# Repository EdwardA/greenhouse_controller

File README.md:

# greenhouse_controller
Arduino and Linux based sensor and control network
As part of a belated Devember

This project is to design and implement a distributed sensor and control system to automate an indoors growing environment.

As the network is designed to automate high volume growing enviroments. Each growing bed utalises its own slave unit which manages and records the data from that bed while passing the data back to the main controller for logging. While also reciving data back from the controller to control the actuators on that bed.

The system will be designed to be expandable very quickly and easily, by adding new 'beds' to the network.

---Slave board---

--Sensors--
Light (intensity and colour)
soil moisture
Soil temperature
Air temperature
RTC (Real Time Clock)

--Control--
Growing lights (LED, RGB)
Sprinklers (Three per bed)
Emergancy Stop
Heater

--Conectivity--
USB (mainly for debug and programming)
Ethernet (Comunicating with the controller)

---Controller Board---
Recive sensor data from slave boards, and send changes in paramaters back.
Most likely Python script
ROS?
Recive changes in parameters from user and distribute relevant commands to slave units.

The slave unit is based off the ATMEGA 1284 chip, using a 3rd party arduino bootloader.

The slave is programed thanks to the use of the bootloader found here: http://www.leonardomiliani.com/repository/package_leonardomiliani.com_index.json

Light sensor = TCSP3200, code based off the example given at: https://randomnerdtutorials.com/arduino-color-sensor-tcs230-tcs3200/

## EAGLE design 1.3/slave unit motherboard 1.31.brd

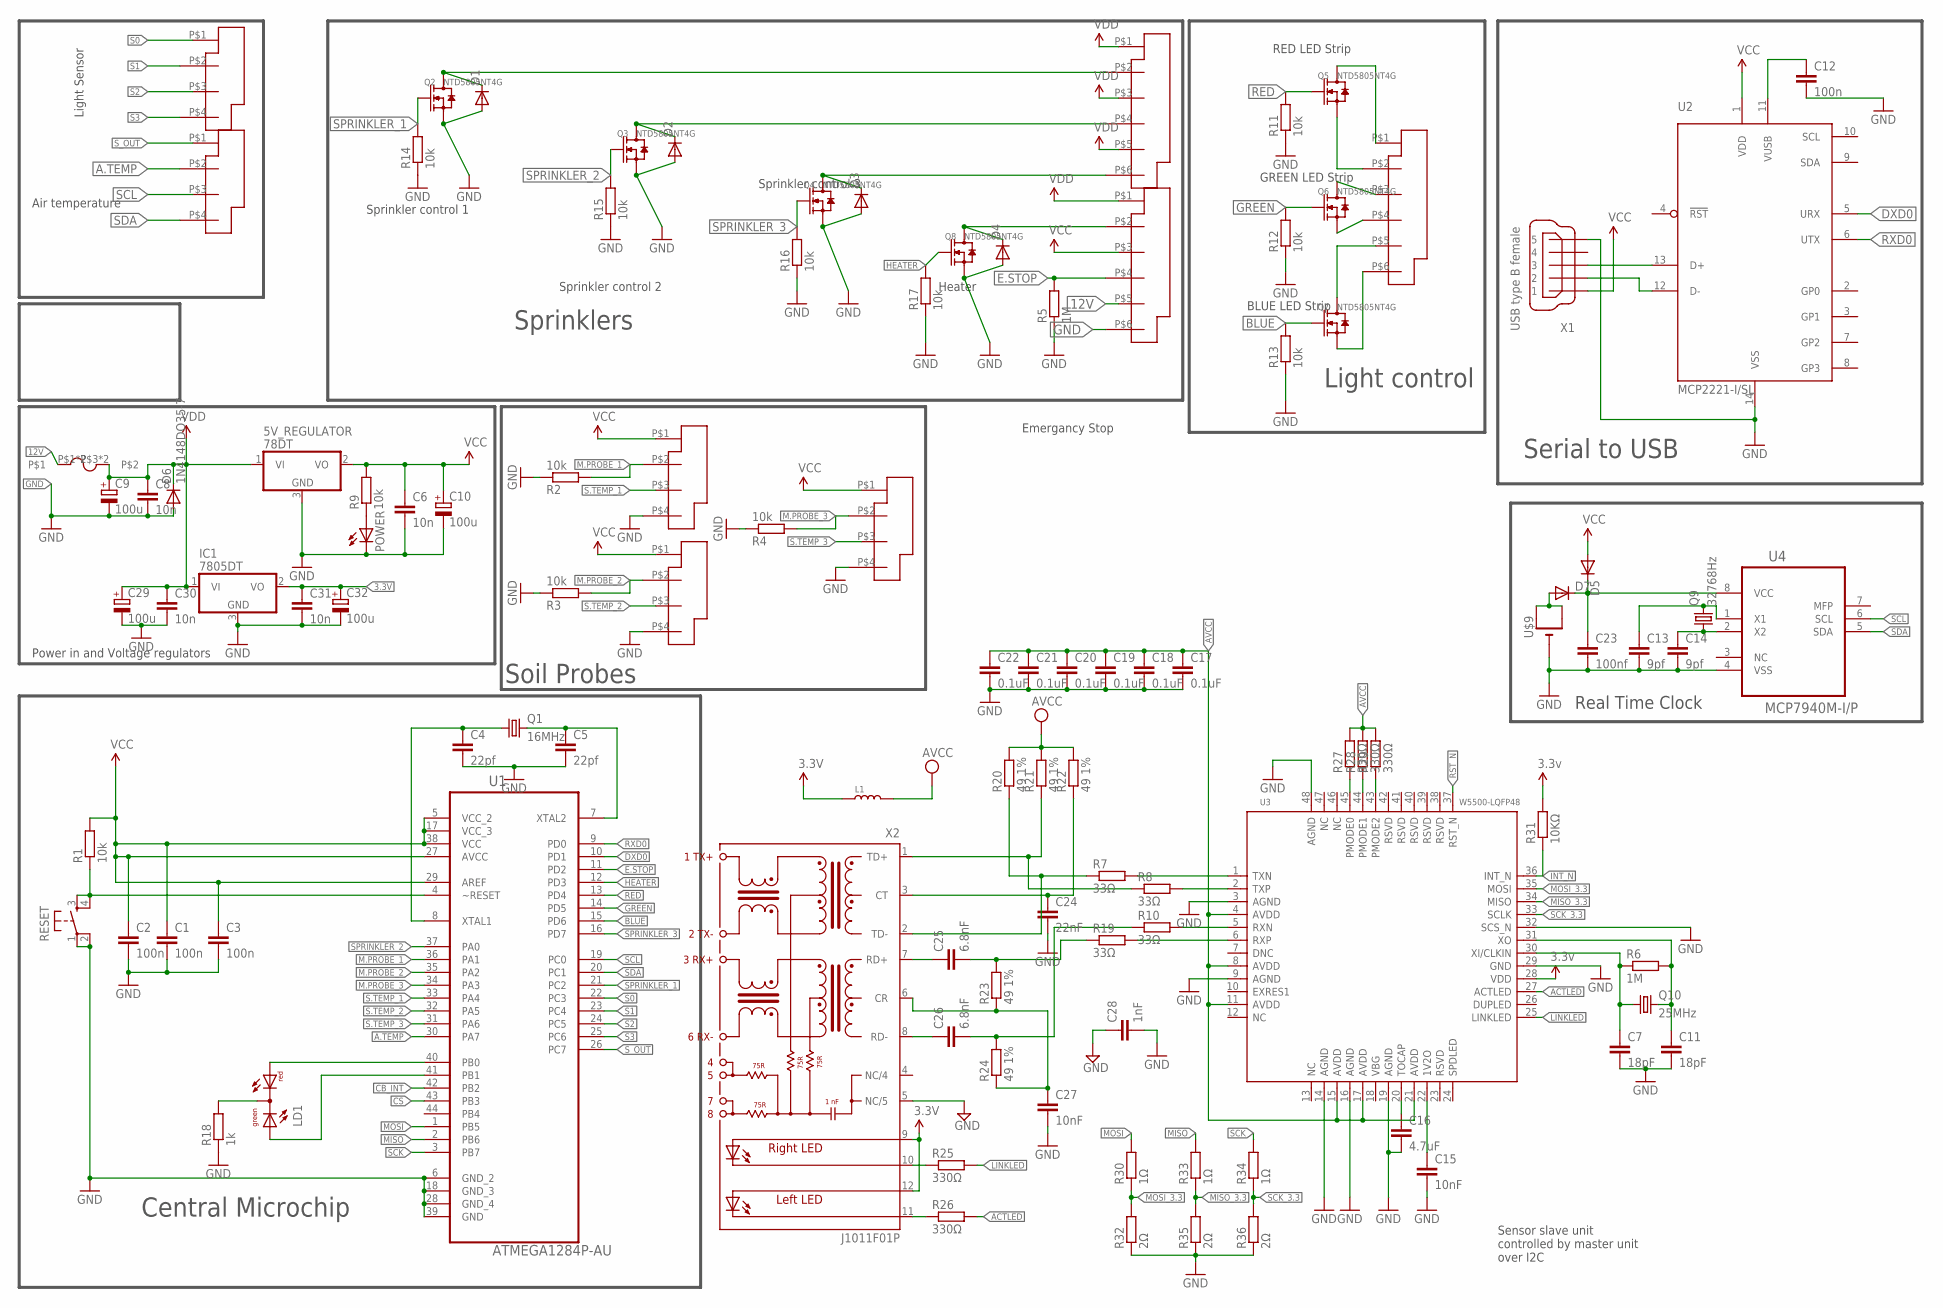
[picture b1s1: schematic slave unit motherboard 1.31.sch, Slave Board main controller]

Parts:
5V_REGULATOR: 78DT; TO252
C1, C2, C3, C12: 100n; C0805
C4, C5: 22pf; C0805
C6, C8, C30, C31: 10n; C0805
C7, C11: 18pF; C0805
C9, C10, C29, C32: 100u; E1,8-4
C13, C14: 9pf; C025-024X044
C15, C27: 10nF; C0805
C16: 4.7uF; C0805
C17, C18, C19, C20, C21, C22: 0.1uF; C0805
C23: 100nf; C025-024X044
C24: 22nF; C0805
C25, C26: 6.8nF; C0805
C28: 1nF; C0805
D1, D2, D3, D4: DIODE-MINIMELF; MINIMELF
D5, D7: DIODE-D-2.5; D-2.5
D6: 1N4148DO35-7; MINIMELF
IC1: 7805DT; TO252
L1: INDUCTOR/FERRITE-BEAD'0805'; L0805
LD1: DUOLED-RG-C; DUOLED-C-5MM
LEDS1: 3X2TERM; 3*2TERM
POWER: LEDLD260; LD260
Q1: 16MHz; HC49
Q2, Q3, Q4, Q8: NTD5805NT4G; SOT-23
Q5, Q6, Q7: NTD5805NT4G; DPAK
Q9: 32768Hz; TC26V
Q10: 25MHz; HC49
R1, R2, R3, R4, R9, R11, R12, R13, R14, R15, R16, R17: 10k; M0805
R5, R6: 1M; M0805
R7, R8, R10, R19: 33Ω; M0805
R18: 1k; M0805
R20, R21, R22, R23, R24: 49 1%; M0805
R25, R26, R27, R28, R29: 330Ω; M0805
R30, R33, R34: 1Ω; M0805
R31: 10KΩ; M0805
R32, R35, R36: 2Ω; M0805
RESET: TACTILE-SWITCH-PTH; TAC-SWITCH-PTH
U1: ATMEGA1284P-AU; QFP80P1200X1200X120-44N
U2: MCP2221-I/SL; SOIC14
U3: W5500-LQFP48; LQFP48-0.5-7X7MM
U4: MCP7940M-I/P; DIP254P762X508-8P
U$1: 520MM_FUSE_HOLDER; 2.5X5MM_FUSE_HOLDER
U$2, U$3, U$4, U$7, U$8: 2X2TERM
U$5, U$6: 3X2TERM; 3*2TERM
U$9: CR1220-THM
X1: USB type B female; 32005-501
X2: J1011F01P; J1

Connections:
3.3V: C31.1, C32.+, IC1.2 (VO), L1.1, R31.2, U3.28 (VDD), X2.9 (A-R), X2.12 (AL)
12V: U$1.P$1, U$1.P$2, U$5.P$5
A.TEMP: U1.30 (PA7), U$3.P$2
ACTLED: R26.2, U3.27 (ACTLED)
AVCC: C17.1, C18.1, C19.1, C20.1, C21.1, C22.1, L1.2, R20.2, R21.2, R22.2, R27.2, R28.2, R29.2, U3.4 (AVDD), U3.8 (AVDD), U3.11 (AVDD), U3.15 (AVDD), U3.17 (AVDD), U3.21 (AVDD)
BLUE: Q7.1 (G), R13.2, U1.15 (PD6)
CB_INT: U1.42 (PB2)
CS: U1.43 (PB3)
DXD0: U1.10 (PD1), U2.5 (URX)
E.STOP: R5.2, U1.11 (PD2), U$5.P$4
EGND: C28.1, X2.5 (NC/5)
ERROR: LD1.AR, U1.40 (PB0)
GND: 5V_REGULATOR.3 (GND), C1.2, C2.2, C3.2, C4.2, C5.2, C6.2, C7.2, C8.2, C9.-, C10.-, C11.2, C12.2, C13.2, C14.2, C15.2, C16.2, C17.2, C18.2, C19.2, C20.2, C21.2, C22.2, C23.2, C24.2, C27.2, C28.2, C29.-, C30.2, C31.2, C32.-, D1.A, D2.A, D3.A, D4.A, D6.A, IC1.3 (GND), POWER.K (C), Q2.2 (S), Q3.2 (S), Q4.2 (S), Q8.2 (S), R2.1, R3.1, R4.1, R5.1, R11.1, R12.1, R13.1, R14.1, R15.1, R16.1, R17.1, R18.1, R32.1, R35.1, R36.1, RESET.1, RESET.2, U1.6 (GND_2), U1.18 (GND_3), U1.28 (GND_4), U1.39 (GND), U2.14 (VSS), U3.3 (AGND), U3.9 (AGND), U3.14 (AGND), U3.16 (AGND), U3.19 (AGND), U3.29 (GND), U3.48 (AGND), U4.4 (VSS), U$4.P$4, U$5.P$6, U$7.P$4, U$8.P$4, U$9.-, X1.5
GREEN: Q6.1 (G), R12.2, U1.14 (PD5)
HEATER: Q8.1 (G), R17.2, U1.12 (PD3)
INT_N: R31.1, U3.36 (INT_N)
LINKLED: R25.2, U3.25 (LINKLED)
M.PROBE_1: R2.2, U1.36 (PA1), U$4.P$2
M.PROBE_2: R3.2, U1.35 (PA2), U$8.P$2
M.PROBE_3: R4.2, U1.34 (PA3), U$7.P$2
MISO: R33.2, U1.2 (PB6)
MISO_3.3: R33.1, R35.2, U3.34 (MISO)
MOSI: R30.2, U1.1 (PB5)
MOSI_3.3: R30.1, R32.2, U3.35 (MOSI)
unnamed: LEDS1.P$1, Q5.3 (D)
unnamed: U2.13 (D+), X1.3
unnamed: C4.1, Q1.1, U1.8 (XTAL1)
unnamed: C5.1, Q1.2, U1.7 (XTAL2)
unnamed: U2.12 (D-), X1.2
unnamed: C23.1, D5.C, D7.C, U4.8 (VCC)
unnamed: LD1.C, R18.2
unnamed: D7.A, U$9.+1 (+), U$9.+2 (+1)
unnamed: D3.C, Q4.3 (D), U$6.P$6
unnamed: LEDS1.P$2, Q5.2 (S)
unnamed: LEDS1.P$3, Q6.3 (D)
unnamed: LEDS1.P$4, Q6.2 (S)
unnamed: LEDS1.P$5, Q7.3 (D)
unnamed: LEDS1.P$6, Q7.2 (S)
unnamed: C7.1, Q10.1, R6.1, U3.30 (XI/CLKIN)
unnamed: C11.1, Q10.2, R6.2, U3.31 (XO)
unnamed: C15.1, U3.22 (1V2O)
unnamed: D4.C, Q8.3 (D), U$5.P$2
unnamed: C12.1, U2.11 (VUSB)
unnamed: C16.1, U3.20 (TOCAP)
unnamed: R7.2, U3.1 (TXN)
unnamed: R8.2, U3.2 (TXP)
unnamed: R10.2, U3.5 (RXN)
unnamed: R19.2, U3.6 (RXP)
unnamed: R7.1, R20.1, X2.2 (TD-)
unnamed: R8.1, R21.1, X2.1 (TD+)
unnamed: POWER.A, R9.1
unnamed: C26.2, R10.1, R24.2
unnamed: C25.2, R19.1, R23.2
unnamed: C24.1, R22.1, X2.3 (CT)
unnamed: C26.1, X2.8 (RD-)
unnamed: C25.1, X2.7 (RD+)
unnamed: C27.1, R23.1, R24.1, X2.6 (CR)
unnamed: R25.1, X2.10 (C-R)
unnamed: R26.1, X2.11 (C-L)
unnamed: R27.1, U3.45 (PMODE0)
unnamed: R28.1, U3.44 (PMODE1)
unnamed: R29.1, U3.43 (PMODE2)
unnamed: C13.1, Q9.2, U4.1 (X1)
unnamed: C14.1, Q9.1, U4.2 (X2)
RED: Q5.1 (G), R11.2, U1.13 (PD4)
RESET: R1.1, RESET.3, RESET.4, U1.4 (~RESET)
RST_N: U3.37 (RST_N)
RUNNING: LD1.AX (AG), U1.41 (PB1)
RXD0: U1.9 (PD0), U2.6 (UTX)
S0: U1.22 (PC3), U$2.P$1
S1: U1.23 (PC4), U$2.P$2
S2: U1.24 (PC5), U$2.P$3
S3: U1.25 (PC6), U$2.P$4
S.TEMP_1: U1.33 (PA4), U$4.P$3
S.TEMP_2: U1.32 (PA5), U$8.P$3
S.TEMP_3: U1.31 (PA6), U$7.P$3
SCK: R34.2, U1.3 (PB7)
SCK_3.3: R34.1, R36.2, U3.33 (SCLK)
SCL: U1.19 (PC0), U4.6 (SCL), U$3.P$3
SCS_N: U3.32 (SCS_N)
SDA: U1.20 (PC1), U4.5 (SDA), U$3.P$4
SPRINKLER_1: Q2.1 (G), R14.2, U1.21 (PC2)
SPRINKLER_2: Q3.1 (G), R15.2, U1.37 (PA0)
SPRINKLER_3: Q4.1 (G), R16.2, U1.16 (PD7)
SPRINKLER_ONE: D1.C, Q2.3 (D), U$6.P$2
SPRINKLER_TWO: D2.C, Q3.3 (D), U$6.P$4
S_OUT: U1.26 (PC7), U$3.P$1
VCC: 5V_REGULATOR.2 (VO), C1.1, C2.1, C3.1, C6.1, C10.+, D5.A, R1.2, R9.2, U1.5 (VCC_2), U1.17 (VCC_3), U1.27 (AVCC), U1.29 (AREF), U1.38 (VCC), U2.1 (VDD), U$4.P$1, U$5.P$3, U$7.P$1, U$8.P$1, X1.1
VDD: 5V_REGULATOR.1 (VI), C8.1, C9.+, C29.+, C30.1, D6.C, IC1.1 (VI), U$1.P$3, U$1.P$4, U$5.P$1, U$6.P$1, U$6.P$3, U$6.P$5

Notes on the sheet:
Power in and Voltage regulators
Sensor slave unit controlled by master unit over I2C
Serial to USB
Central Microchip
RED LED Strip
GREEN LED Strip
BLUE LED Strip
Light Sensor
Light control
Sprinkler control 1
Sprinkler control 2
Sprinkler control 3
Sprinklers
Soil Probes
Air temperature
Heater
Emergancy Stop
Real Time Clock

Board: 2 copper layers, 107 parts (0 on the bottom side), 85 nets, no tracks yet.

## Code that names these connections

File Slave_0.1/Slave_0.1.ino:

//Libraries
#include <PID_v1.h>


//---INPUTS---

//Moisture Probes
const int moisture_One = A1;
int moisture_One_Val = 0;
const int moisture_Two = A2;
int moisture_Two_Val = 0;
const int moisture_Three = A3;
int moisture_Three_Val = 0;

//Temperature Sensor
const int temp_One = A4;
int temp_One_Val = 0;
const int temp_Two = A5;
int temp_Two_Val = 0;
const int temp_Three = A6;
int temp_Three_Val = 0;

//Air Temperature Sensor
const int temp_Air = A7;
int temp_Air_Val = 0;

//Light colour sensor
const int S0 = 19;
const int S1 = 20;
const int S2 = 21;
const int S3 = 22;
const int S_Out = 23;

int red_Freq = 0;
int green_Freq = 0;
int blue_Freq = 0;

double red_Colour = 0;
double red_Setpoint = 0;
double green_Colour = 0;
double green_Setpoint = 0;
double blue_Colour = 0;
double blue_Setpoint = 0;


//---OUTPUTS---

//Sprinklers
const int sprinkler_One = 18;
int sprinkler_One_Val = 0;
const int sprinkler_Two = 24;
int sprinkler_Two_Val = 0;
const int sprinkler_Three = 15;
int sprinkler_Three_Val = 0;

//Heater
const int heater = 11;
int heater_Val = 0;

//Emergancy Stop
const int E_Stop = 10;
volatile byte emergancy = LOW;

//RGB LEDs
const int red = 12;
int red_Val = 0;
const int green = 13;
int green_Val = 0;
const int blue = 14;
int blue_Val = 0;

//---OTHER---


double Kp = 0;
double Ki = 0;
double Kd = 0;

PID red_PID(red_Colour, red_Val, red_Setpoint, Kp, Ki, Kd, DIRECT);
PID green_PID(green_Colour, green_Val, green_Setpoint, Kp, Ki, Kd, DIRECT);
PID blue_PID(blue_Colour, blue_Val, blue_Setpoint, Kp, Ki, Kd, DIRECT);


void setup() {
  //Sprinklers
  pinMode(sprinkler_One, OUTPUT);
  pinMode(sprinkler_Two, OUTPUT);
  pinMode(sprinkler_Three, OUTPUT);

  //Heater
  pinMode(heater, OUTPUT);

  //Emergancy Stop
  pinMode(E_Stop,INPUT);
  attachInterrupt(25,emergancy_Stop, LOW);

  //RGB LEDs
  pinMode(red, OUTPUT);
  pinMode(green, OUTPUT);
  pinMode(blue, OUTPUT);

  //Light colour sensor
  pinMode(S0, OUTPUT);
  pinMode(S1, OUTPUT);
  pinMode(S2, OUTPUT);
  pinMode(S3, OUTPUT);
  
  pinMode(S_Out, INPUT);
  
  digitalWrite(S0,HIGH); //sets the frequency scaling to 20%
  digitalWrite(S1,LOW);


  red_PID.SetMode(AUTOMATIC);
  green_PID.SetMode(AUTOMATIC);
  blue_PID.SetMode(AUTOMATIC);
}

void loop() {
  

}

void colour_Check(){
  digitalWrite(S2,LOW); //set sensor to read red value
  digitalWrite(S3,LOW);

  red_Freq = pulseIn(S_Out,LOW); //Read red value
  red_Colour = map(red_Freq, 0,100,255,0); // maps red sensor output to standard RGB range **Change input values to map to within appropriate range after testing**
  delay(100);
  
  digitalWrite(S2,HIGH); //set sensor to read green value
  digitalWrite(S3,HIGH);

  green_Freq = pulseIn(S_Out,LOW); //Read red value
  green_Colour = map(green_Freq, 0,100,255,0); // maps green sensor output to standard RGB range **Change input values to map to within appropriate range after testing**
  delay(100);

  digitalWrite(S2,LOW); //set sensor to read blue value
  digitalWrite(S3,HIGH);

  blue_Freq = pulseIn(S_Out,LOW);
  blue_Colour = map(blue_Freq, 0,100,255,0); // maps blue sensor output to standard RGB range **Change input values to map to within appropriate range after testing**
  delay(100);

  //PID light control

  while (red_Colour != red_Setpoint) {
    red_PID.Compute();
  }
  while (green_Colour != green_Setpoint) {
    green_PID.Compute();
  }
  while (blue_Colour != blue_Setpoint) {
    blue_PID.Compute();
  }
}

void emergancy_Stop(){
  
}

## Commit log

2017-12-13 Added project details to README
2017-12-14 Added schematic and PCB design files
    1.3 is the current most recent version of the hardware for the slave sensor unit.
2017-12-14 Updated readme with chip details
2017-12-14 Added URL link to the custom bootloader
2017-12-14 ATMEGA 1284p arduino pinout added
2017-12-14 Added sprinkler pin constants to ardunio sketch
2017-12-14 Corrected sintax mistake
2017-12-14 Corrected image for TQFP44 package
2017-12-14 Added sensor input constants
2017-12-15 Updated README with project desired outcomes
2017-12-15 Added all connect pin integers
2017-12-15 Added pinMode for all pins
2017-12-15 Added Light colour sensor code, added link to README and contributed to void setup
2017-12-15 Corrected indent
2017-12-15 Corrected syntax error
2017-12-15 Started adding PID control for the LEDs, however I am having an issue with the syntax for the PID control library.

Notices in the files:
parts and their libraries:
GeekAmmo: Licensing:Creative Commons ShareAlike 4.0 International - https://creativecommons.org/licenses/by-sa/4.0
